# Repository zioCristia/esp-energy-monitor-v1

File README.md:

# Esp energy monitor - Version 1
### There is a new and better [version](https://github.com/zioCristia/esp-energy-monitor-v2) of this board
Esp32 based module, 220V ac powered, energy monitor with two ct sensors for solar power and home power, and an LCD I2C display for visualization. Integrated with ESPhome in my IoT house based in Home Assistant.
Any possibility of improvement is accepted.

You can find a [video tutorial](https://www.youtube.com/watch?v=UY-CO4Zc2r0) (in italian) of this pcb on YouTube.

### Disclaimer! The current pcb design is not the one you can see in the phote above but a new one with jack connectors that are more easily found in the online market. See the [pcb section](#pcb) for more info.

## Table of contents
* [General info](#general-info)
* [Hardware](#hardware)
* [Software](#software)
* [Pcb](#pcb)
* [Contribution](#contribution)

# General info
This is an extremely simple power monitor that I built for my house. It has two ct-sensors which control the current of solar panels production and house consumption. These sensors are controlled by an esp32 board for the connectivity with wi-fi to home assistant thanks to Esphome software. 
The board is powered with a 220v ac, so no external transformer is needed. 

I have also added a 16x2 lcd so that to have an immediate output in my electrical service panel.

You could use this board also if you want to use just on ct-sensor and maybe add it later on. The total cost for a board with two ct sensors (included) is around 20/25€.

In the future I'm planning to add one other ct-sensor for conditioning power consumption and to add an irrigation system for my garden as the current irrigation system controller is near the service panel.

# Hardware
The module is composed of:
* esp32
* sct 013 030 30A/1V as ct sensor, x2
* 16x2 lcd display with i2c interface
* 3.5mm jack connector with 5 pin, x2
* 10k ohm resistor, x4
* 75ohm resistor, x2
* 10uF capacitor, x3

To have the best readings, the 75ohm resistor should be changed based on the max current you are going to measure with the ct sensors, according to the following formula present in [openenergymonitor](https://learn.openenergymonitor.org/electricity-monitoring/ct-sensors/interface-with-arduino) page:
```
Burden Resistor (ohms) = (AREF * CT TURNS) / (2√2 * max primary current)
```
I've used 75 ohm resistor as I'm not going to measure currents higher than 26A.

Of course, if you'd want just one ct sensor and you should use 2x 10k ohm resistors, 75ohm resistor and 10uF capacitor less from the components.
I'm planning to make a version with the normal jack connector directly soldered in the pcb.

You can find some components links [here](https://docs.google.com/spreadsheets/d/1uGH7hN6ZSQ5MoKFjuWFCn1lEjyLJ1oxg2DWpdToigKc/edit?usp=sharing).

# Software
The software used is EspHome in order to integrate the sensor with my HomeAssistant server but you may as well use another software to your liking.

You can find an example of the code I used [here](https://github.com/zioCristia/esp-energy-monitor-v1/blob/main/energy-monitor.yaml.example) or check in the [openenergymonitor](https://learn.openenergymonitor.org/electricity-monitoring/ct-sensors/how-to-build-an-arduino-energy-monitor-measuring-current-only?redirected=true) site for others examples.

The filter section is used to obtain the right value of current from the sensor. I've done it confronting the values read with a well know source (like a phone or an electric heater).
Moreover I've added a part to read zero values when we are near zero due to some interference that never allows to have values equal to zero.
```
filters:
      - calibrate_linear:
          # Measured value of 0.0065 maps to 0A
          - 0.0065 -> 0
          # Known load: 13.783A
          # Value shown in logs: 0.2348A
          - 0.2348 -> 13.783
      - lambda: |-
          if (x > 0.2) return x;
          else return 0;
```

I've added a software sensor which gives me the difference between the in power and the out power with which I do some automation in home assistant and allows me to maximize the usage of current produced by the solar panels.

The toGridEnergy and the toGridPower is used to interface with the new energy management feature in home assistant.

The lcd prints the solar power as IN, home power as OUT, the hour in the top right and below the difference between IN-OUT, so the differencePower.

# Pcb
The pcb layout is extremely simple with enough space for all the parts. The components are all through hole and the female jack connector is with 5 pins. Anyone can make this pcb at home with just a soldering iron.
As can be seen in the image below, the circuit board has been modified to make it easier to replicate. The jack connector used is more easily found in any store for a few euros. 

You can find the whole eagle project in [this folder](https://github.com/zioCristia/esp-energy-monitor-v1/tree/main/pcb-energy_monitor_v1).

# Contribution
Feel free to report any bugs or feature requests.

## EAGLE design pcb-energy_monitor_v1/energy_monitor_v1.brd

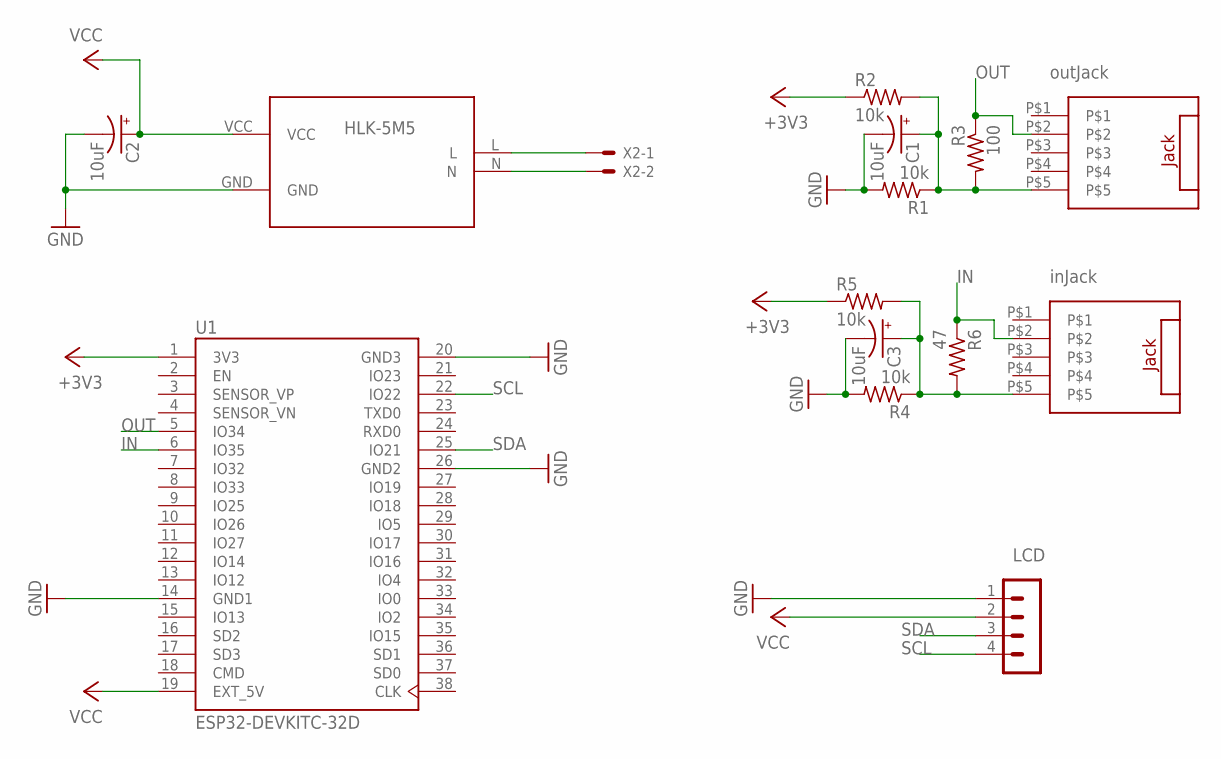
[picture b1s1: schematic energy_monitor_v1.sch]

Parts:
C1, C2, C3: 10uF; B45181A
HLK-5M5: HLK-5M05; CONV_HLK-5M05
R1, R2, R4, R5: 10k; 0204/7
R3: 100; 0204/7
R6: 47; 0204/7
SV3: MA04-1
U1: ESP32-DEVKITC-32D; MODULE_ESP32-DEVKITC-32D
U$1, U$2: JACK_5PINS
X2: JST-XH-02-PIN-LONG-PAD; JST-XH-02-PACKAGE-LONG-PAD

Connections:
+3V3: R2.1, R5.1, U1.1 (3V3)
GND: C1.-, C2.-, C3.-, HLK-5M5.GND, R1.2, R4.2, SV3.1, U1.14 (GND1), U1.20 (GND3), U1.26 (GND2)
IN: R6.1, U1.6 (IO35), U$2.P$2
unnamed: HLK-5M5.N, X2.2
unnamed: HLK-5M5.L, X2.1
unnamed: C1.+, R1.1, R2.2, R3.2, U$1.P$5
unnamed: C3.+, R4.1, R5.2, R6.2, U$2.P$5
OUT: R3.1, U1.5 (IO34), U$1.P$2
SCL: SV3.4, U1.22 (IO22)
SDA: SV3.3, U1.25 (IO21)
VCC: C2.+, HLK-5M5.VCC, SV3.2, U1.19 (EXT_5V)

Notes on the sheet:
HLK-5M5
inJack
outJack
LCD

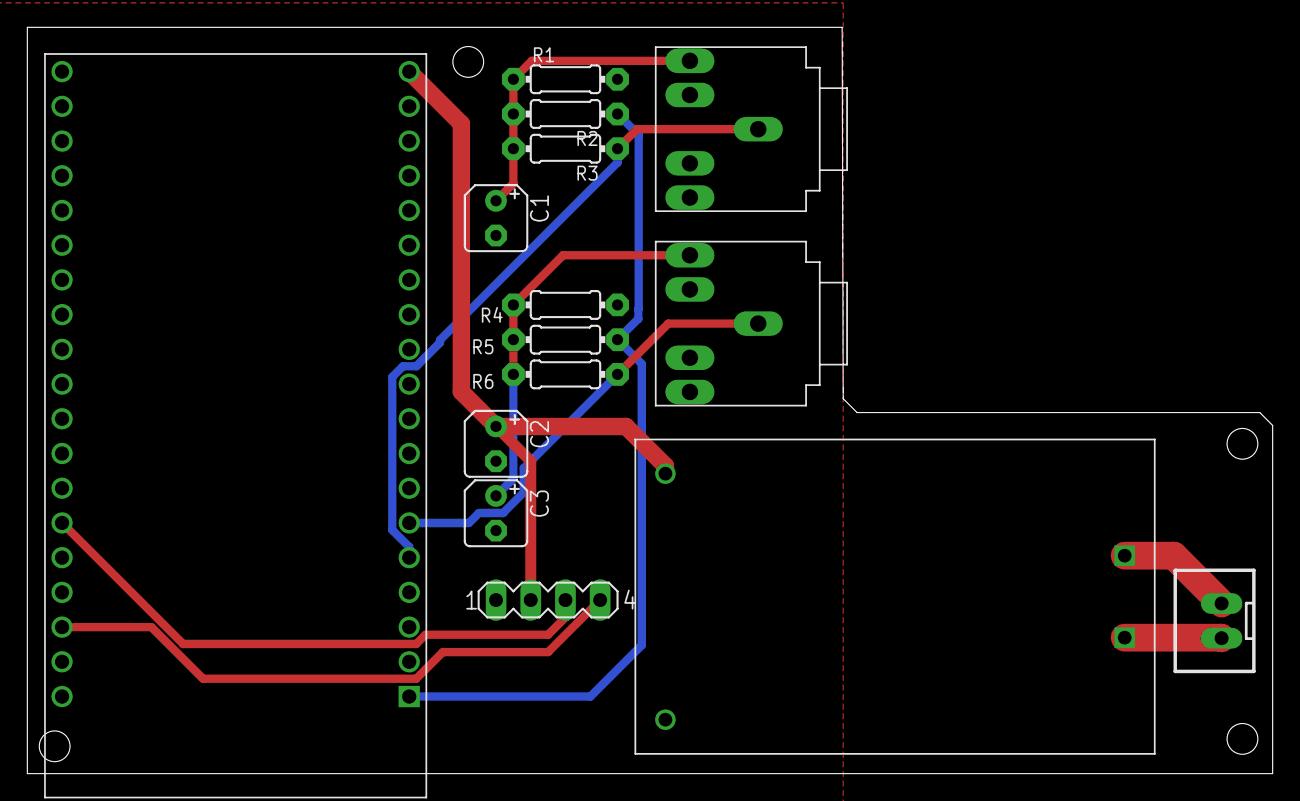
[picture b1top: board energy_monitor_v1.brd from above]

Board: 2 copper layers, 91.1 x 54.6 mm, 15 parts (0 on the bottom side), 11 nets.

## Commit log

2022-07-22 Set theme jekyll-theme-minimal
